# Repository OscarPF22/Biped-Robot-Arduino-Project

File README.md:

# Biped-Robot-Arduino-Project
This repository contains all the main files involved in the development of the Final degree project in Electronic Systems Engineering from the University of Malaga.
- PCB_ESP32_UnaCara_Galgas: This folder contains all the files from the KiCad project (PCI/PCB development).
- STL Biped Robot: This folder contains all the STL files of the 3D printed parts used to build the robot.
- analog_pid_IMU_esp32_v2: This folder contains the Arduino codes for the stability control (the analog part is commented and not used).
- ik_v14_esp32: This folder contains the Arduino codes for making the robot walk (mainly inverse kinematics).

Walking demo video:

<p align="center">
  
</p>

Stabilization demo video:

<p align="center">
  
</p>

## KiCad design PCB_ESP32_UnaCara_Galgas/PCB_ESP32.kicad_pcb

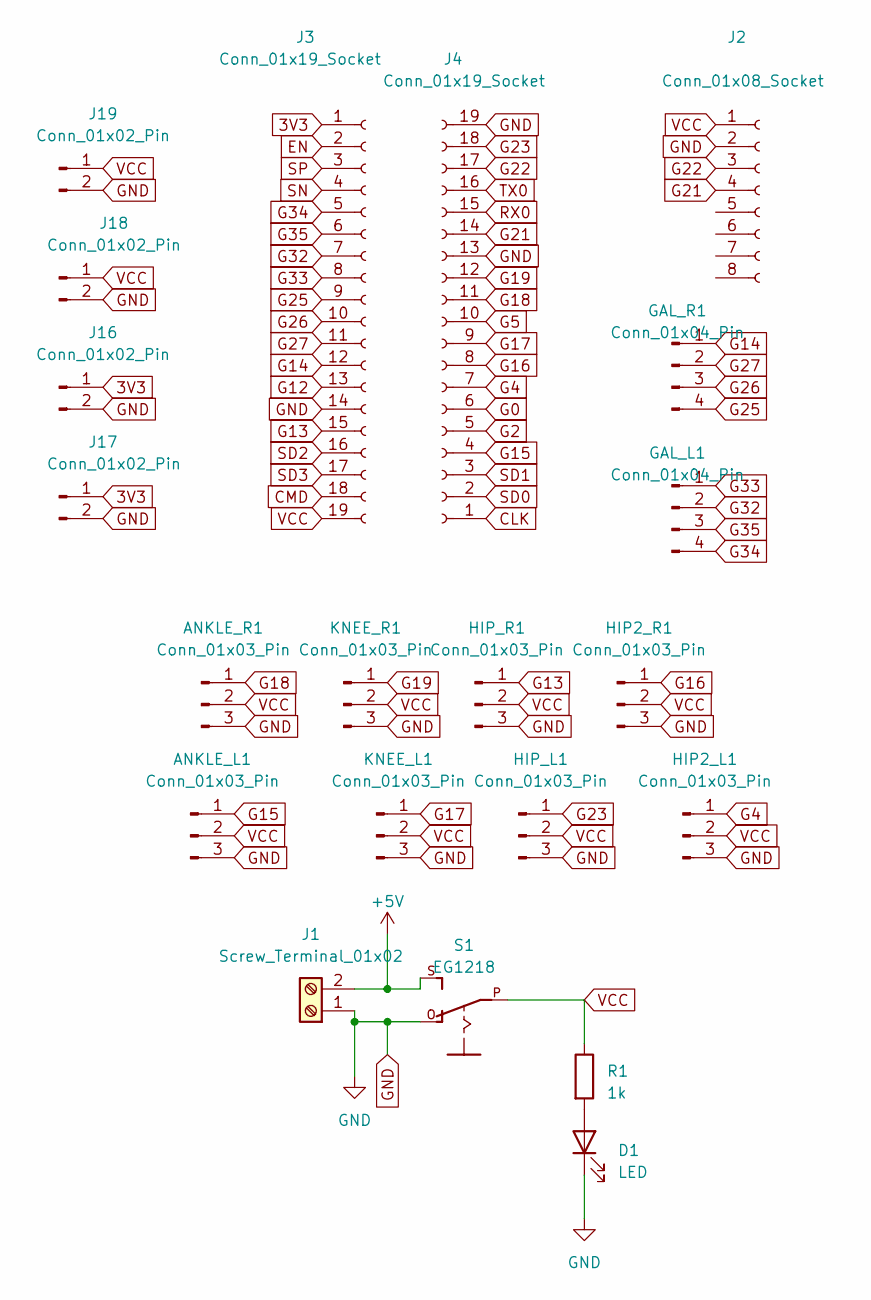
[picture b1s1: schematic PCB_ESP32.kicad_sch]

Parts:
ANKLE_L1: Conn_01x03_Pin; PinHeader_1x03_P2.54mm_Vertical
ANKLE_R1: Conn_01x03_Pin; PinHeader_1x03_P2.54mm_Vertical
D1: LED; LED_D3.0mm
GAL_L1: Conn_01x04_Pin; PinHeader_1x04_P2.54mm_Vertical
GAL_R1: Conn_01x04_Pin; PinHeader_1x04_P2.54mm_Vertical
HIP2_L1, HIP2_R1: Conn_01x03_Pin; PinHeader_1x03_P2.54mm_Vertical
HIP_L1: Conn_01x03_Pin; PinHeader_1x03_P2.54mm_Vertical
HIP_R1: Conn_01x03_Pin; PinHeader_1x03_P2.54mm_Vertical
J1: Screw_Terminal_01x02; TerminalBlock_Altech_AK300-2_P5.00mm
J2: Conn_01x08_Socket; PinSocket_1x08_P2.54mm_Vertical
J3, J4: Conn_01x19_Socket; PinSocket_1x19_P2.54mm_Vertical
J16, J17, J18, J19: Conn_01x02_Pin; PinHeader_1x02_P2.54mm_Vertical
KNEE_L1: Conn_01x03_Pin; PinHeader_1x03_P2.54mm_Vertical
KNEE_R1: Conn_01x03_Pin; PinHeader_1x03_P2.54mm_Vertical
R1: 1k; R_Axial_DIN0204_L3.6mm_D1.6mm_P5.08mm_Horizontal
S1: EG1218

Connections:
3V3: J3.1, J16.1, J17.1
+5V: J1.2, S1.S
CLK: J4.1
CMD: J3.18
EN: J3.2
G0: J4.6
G2: J4.5
G4: HIP2_L1.1, J4.7
G5: J4.10
G12: J3.13
G13: HIP_R1.1, J3.15
G14: GAL_R1.1, J3.12
G15: ANKLE_L1.1, J4.4
G16: HIP2_R1.1, J4.8
G17: J4.9, KNEE_L1.1
G18: ANKLE_R1.1, J4.11
G19: J4.12, KNEE_R1.1
G21: J2.4, J4.14
G22: J2.3, J4.17
G23: HIP_L1.1, J4.18
G25: GAL_R1.4, J3.9
G26: GAL_R1.3, J3.10
G27: GAL_R1.2, J3.11
G32: GAL_L1.2, J3.7
G33: GAL_L1.1, J3.8
G34: GAL_L1.4, J3.5
G35: GAL_L1.3, J3.6
GND: ANKLE_L1.3, ANKLE_R1.3, D1.1 (K), HIP2_L1.3, HIP2_R1.3, HIP_L1.3, HIP_R1.3, J1.1, J2.2, J3.14, J4.13, J4.19, J16.2, J17.2, J18.2, J19.2, KNEE_L1.3, KNEE_R1.3, S1.O
unnamed: D1.2 (A), R1.2
RX0: J4.15
SD0: J4.2
SD1: J4.3
SD2: J3.16
SD3: J3.17
SN: J3.4
SP: J3.3
TX0: J4.16
VCC: ANKLE_L1.2, ANKLE_R1.2, HIP2_L1.2, HIP2_R1.2, HIP_L1.2, HIP_R1.2, J2.1, J3.19, J18.1, J19.1, KNEE_L1.2, KNEE_R1.2, R1.1, S1.P

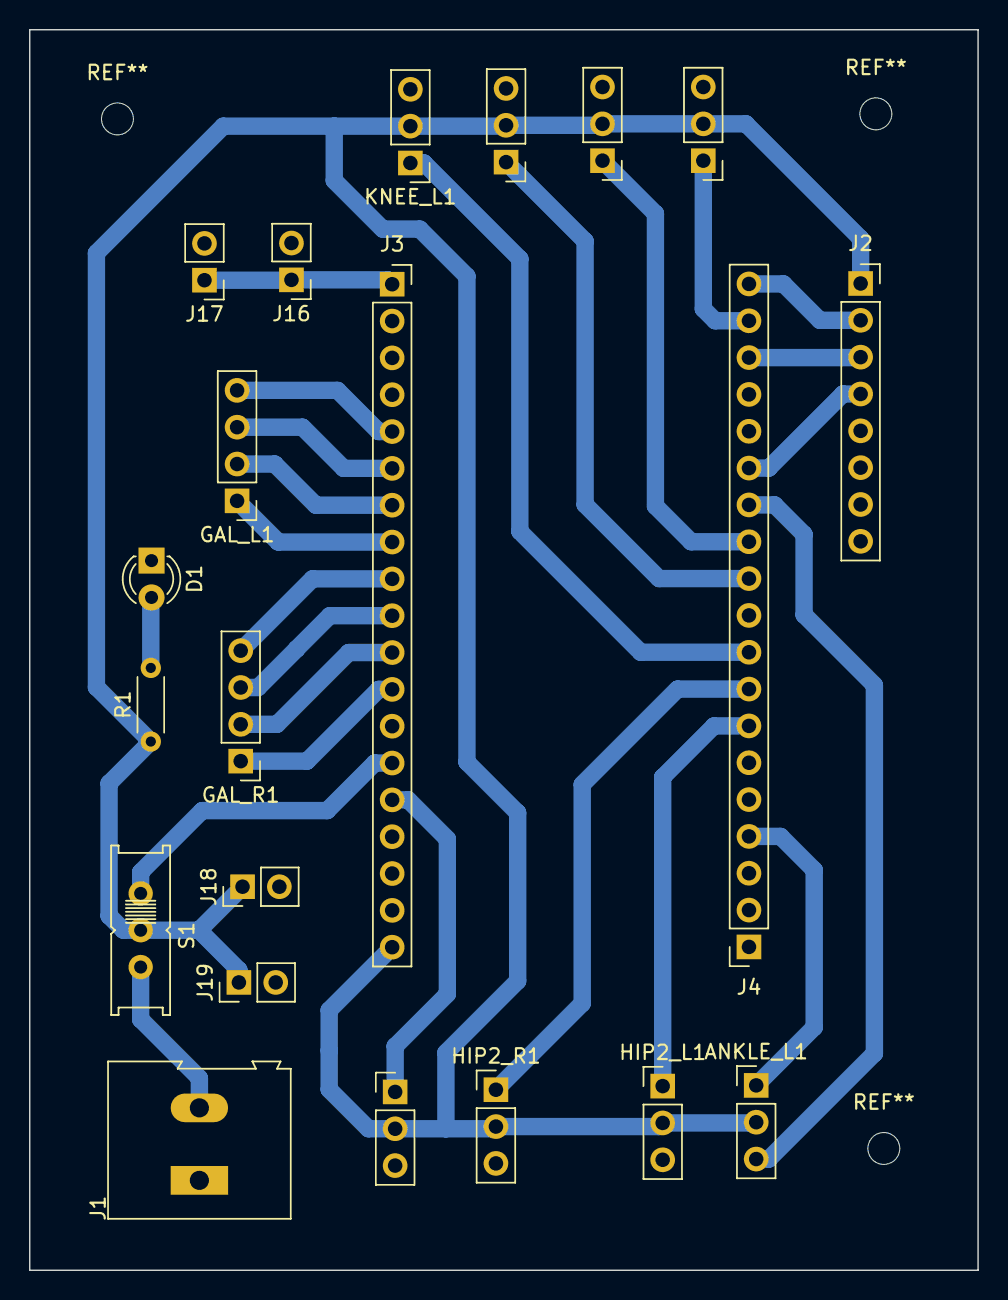
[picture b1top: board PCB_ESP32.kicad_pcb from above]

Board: 2 copper layers, 65.4 x 85.5 mm, 21 parts (0 on the bottom side), 23 nets.

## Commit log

2024-01-05 upload files
2024-01-05 upload photo
2024-01-05 upload missing STL file
2024-02-09 upload pid controller
